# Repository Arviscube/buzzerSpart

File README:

## INSTALLATION
- git clone
- sudo apt install nodejs
- sudo apt install npm
- npm install

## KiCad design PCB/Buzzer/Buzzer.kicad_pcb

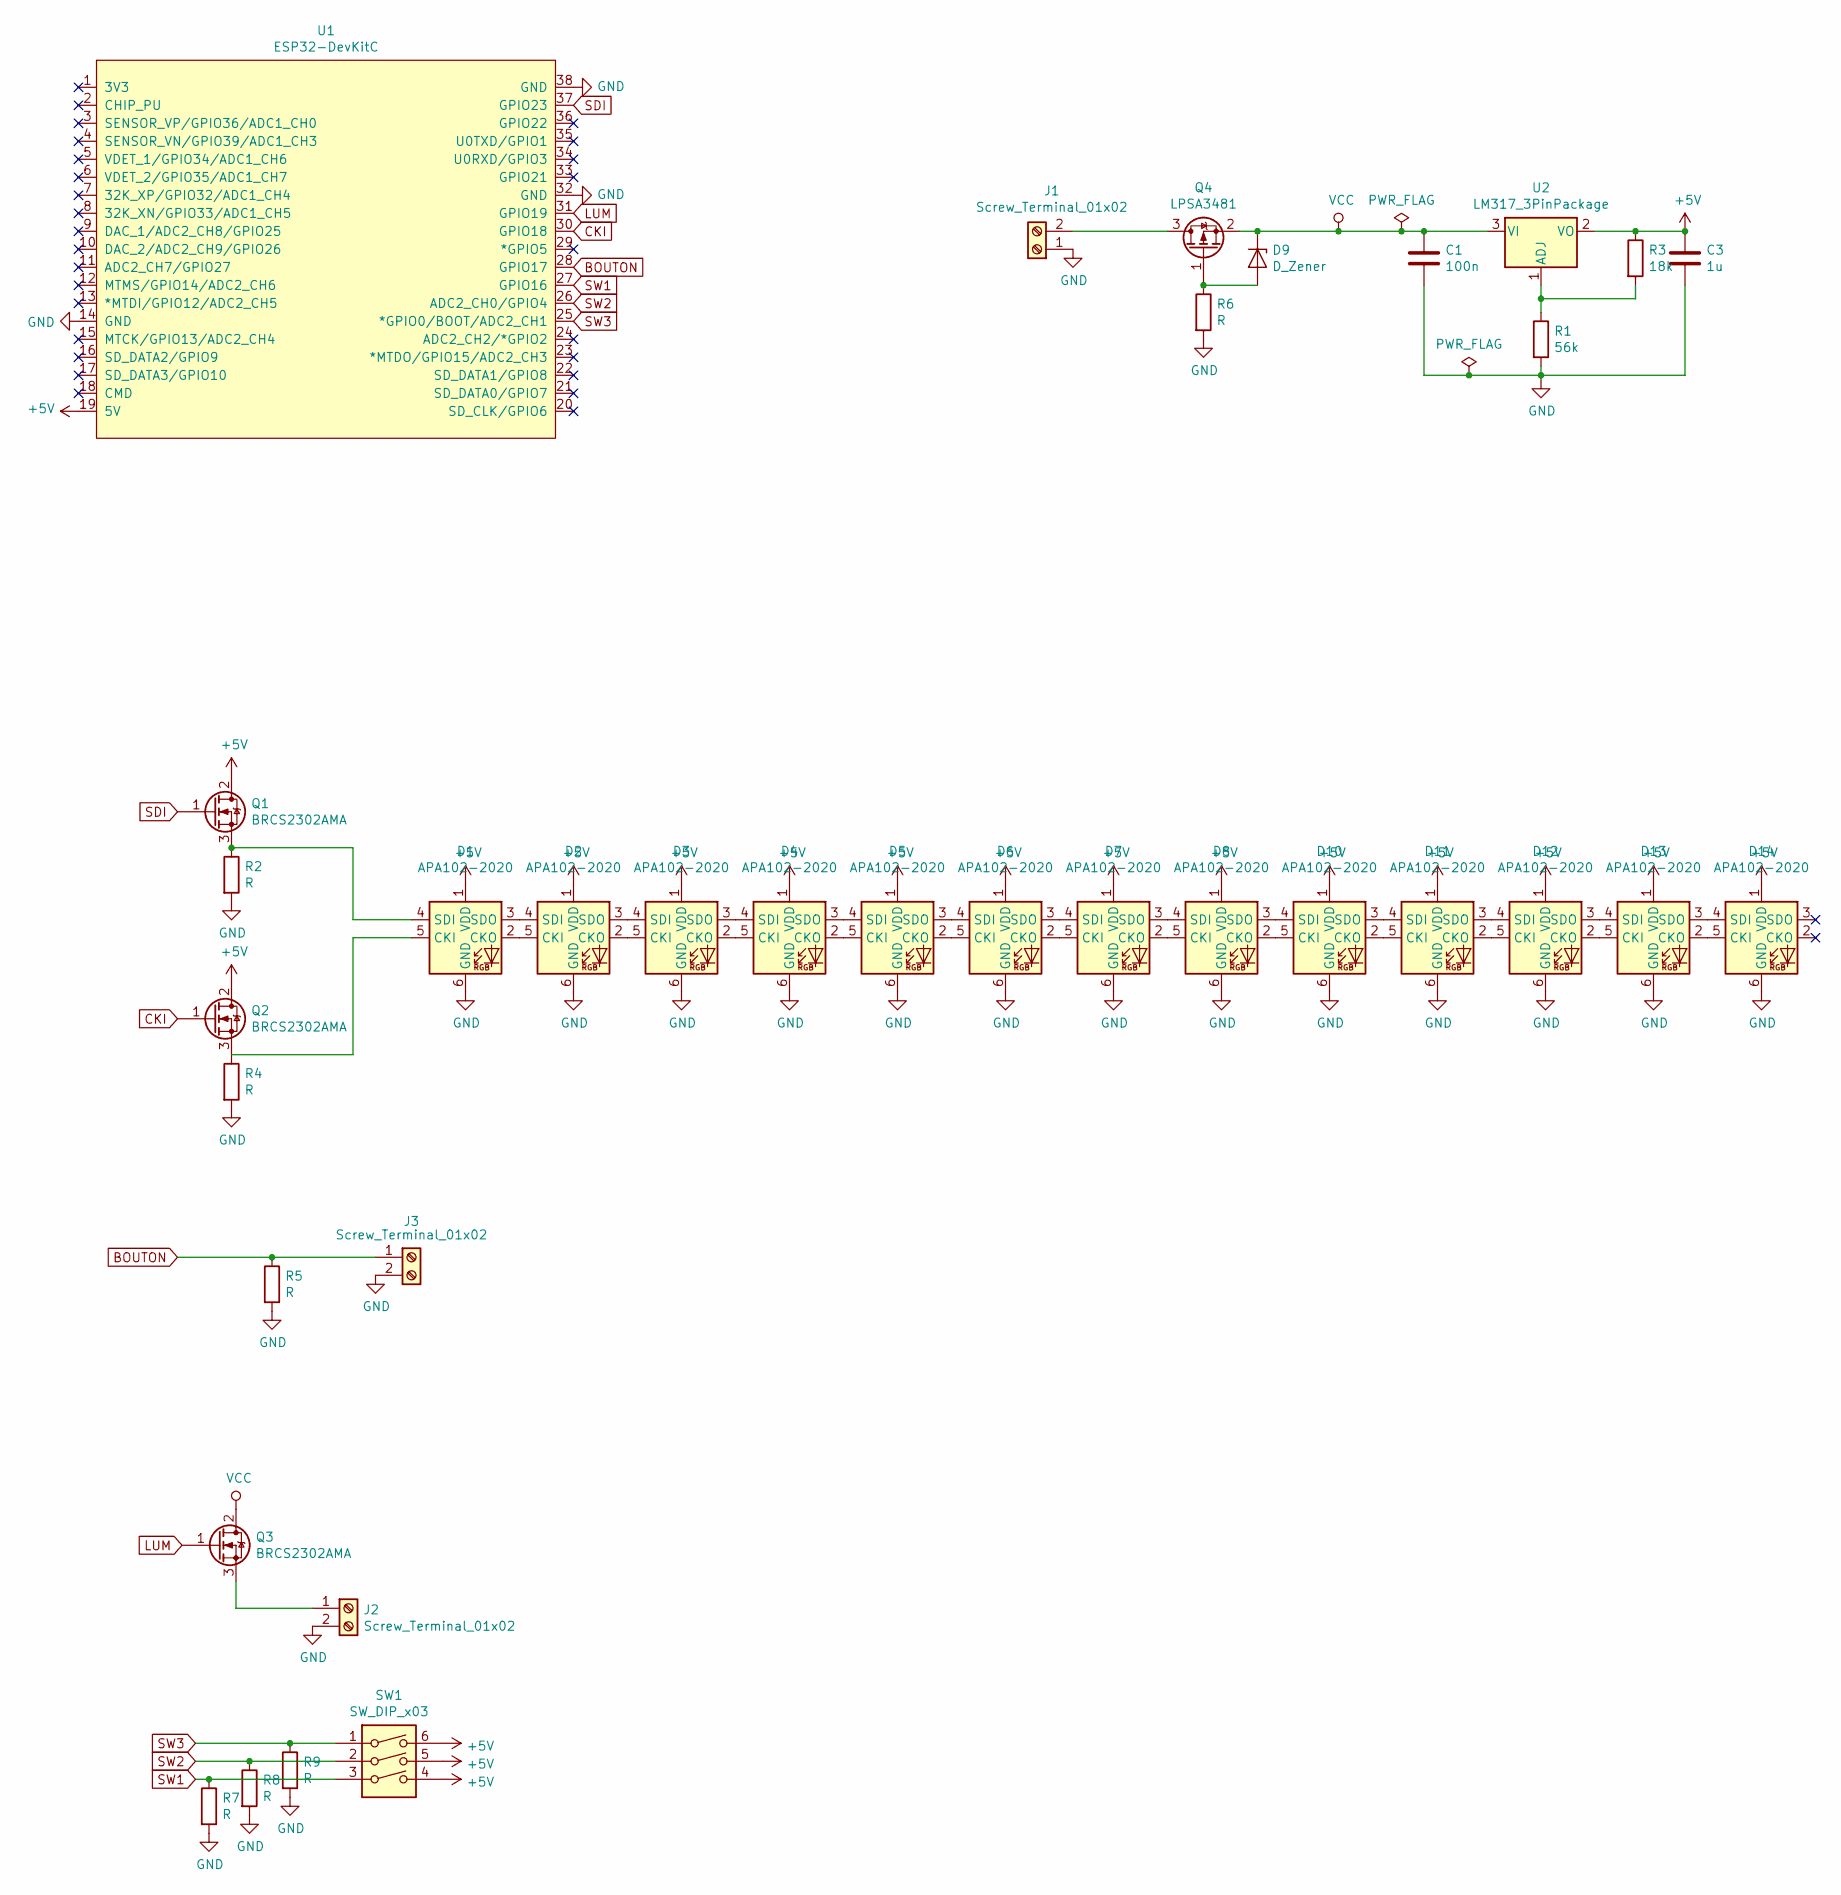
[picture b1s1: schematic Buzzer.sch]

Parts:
C1: 100n; C_0805_2012Metric
C3: 1u; C_0805_2012Metric
D1, D2, D3, D4, D5, D6, D7, D8, D10, D11, D12, D13, D14: APA102-2020; LED-APA102-2020
D9: D_Zener; D_SOD-123
J1, J2, J3: Screw_Terminal_01x02; TerminalBlock_bornier-2_P5.08mm
Q1, Q2, Q3: BRCS2302AMA; SOT-23
Q4: LPSA3481; SOT-23
R1: 56k; R_0805_2012Metric
R2, R4, R5, R6, R7, R8, R9: R; R_0805_2012Metric
R3: 18k; R_0805_2012Metric
SW1: SW_DIP_x03; SW_DIP_SPSTx03_Slide_9.78x9.8mm_W7.62mm_P2.54mm
U1: ESP32-DevKitC
U2: LM317_3PinPackage; TO-252-2

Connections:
+5V: C3.1, D1.1 (VDD), D2.1 (VDD), D3.1 (VDD), D4.1 (VDD), D5.1 (VDD), D6.1 (VDD), D7.1 (VDD), D8.1 (VDD), D10.1 (VDD), D11.1 (VDD), D12.1 (VDD), D13.1 (VDD), D14.1 (VDD), Q1.2 (D), Q2.2 (D), R3.1, SW1.4, SW1.5, SW1.6, U1.19 (5V), U2.2 (VO)
BOUTON: J3.1, R5.1, U1.28 (GPIO17)
CKI: Q2.1 (G), U1.30 (GPIO18)
GND: C1.2, C3.2, D1.6 (GND), D2.6 (GND), D3.6 (GND), D4.6 (GND), D5.6 (GND), D6.6 (GND), D7.6 (GND), D8.6 (GND), D10.6 (GND), D11.6 (GND), D12.6 (GND), D13.6 (GND), D14.6 (GND), J1.1, J2.2, J3.2, R1.2, R2.2, R4.2, R5.2, R6.2, R7.2, R8.2, R9.2, U1.14 (GND), U1.32 (GND), U1.38 (GND)
LUM: Q3.1 (G), U1.31 (GPIO19)
unnamed: D1.2 (CKO), D2.5 (CKI)
unnamed: D1.3 (SDO), D2.4 (SDI)
unnamed: D1.4 (SDI), Q1.3 (S), R2.1
unnamed: D1.5 (CKI), Q2.3 (S), R4.1
unnamed: D2.2 (CKO), D3.5 (CKI)
unnamed: D2.3 (SDO), D3.4 (SDI)
unnamed: D3.2 (CKO), D4.5 (CKI)
unnamed: D3.3 (SDO), D4.4 (SDI)
unnamed: D4.2 (CKO), D5.5 (CKI)
unnamed: D4.3 (SDO), D5.4 (SDI)
unnamed: D5.2 (CKO), D6.5 (CKI)
unnamed: D5.3 (SDO), D6.4 (SDI)
unnamed: D6.2 (CKO), D7.5 (CKI)
unnamed: D6.3 (SDO), D7.4 (SDI)
unnamed: D7.2 (CKO), D8.5 (CKI)
unnamed: D7.3 (SDO), D8.4 (SDI)
unnamed: D9.2 (A), Q4.1 (G), R6.1
unnamed: D10.2 (CKO), D11.5 (CKI)
unnamed: D10.3 (SDO), D11.4 (SDI)
unnamed: D8.3 (SDO), D10.4 (SDI)
unnamed: D8.2 (CKO), D10.5 (CKI)
unnamed: D11.2 (CKO), D12.5 (CKI)
unnamed: D11.3 (SDO), D12.4 (SDI)
unnamed: D12.2 (CKO), D13.5 (CKI)
unnamed: D12.3 (SDO), D13.4 (SDI)
unnamed: D13.2 (CKO), D14.5 (CKI)
unnamed: D13.3 (SDO), D14.4 (SDI)
unnamed: J1.2, Q4.3 (D)
unnamed: J2.1, Q3.3 (S)
unnamed: R1.1, R3.2, U2.1 (ADJ)
SDI: Q1.1 (G), U1.37 (GPIO23)
SW1: R7.1, SW1.3, U1.27 (GPIO16)
SW2: R8.1, SW1.2, U1.26 (ADC2_CH0/GPIO4)
SW3: R9.1, SW1.1, U1.25 (*GPIO0/BOOT/ADC2_CH1)
VCC: C1.1, D9.1 (K), Q3.2 (D), Q4.2 (S), U2.3 (VI)

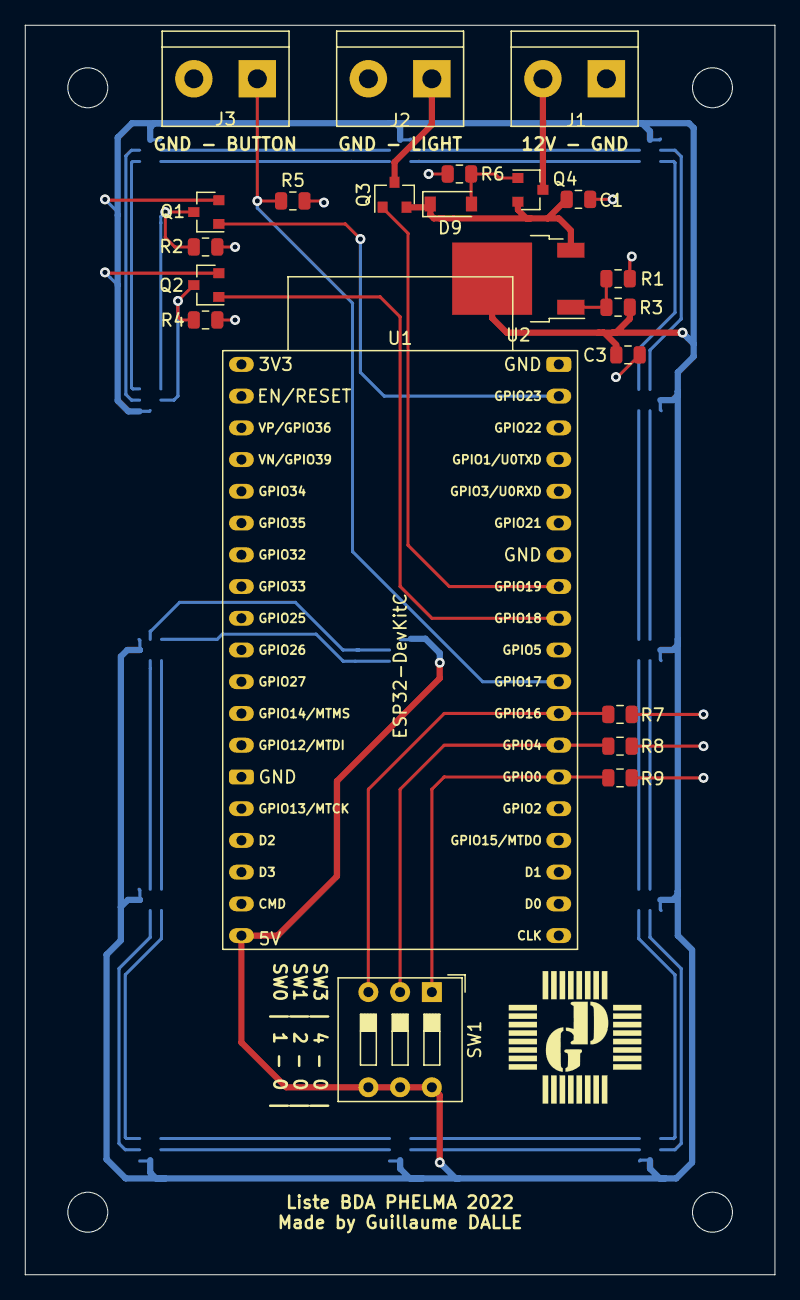
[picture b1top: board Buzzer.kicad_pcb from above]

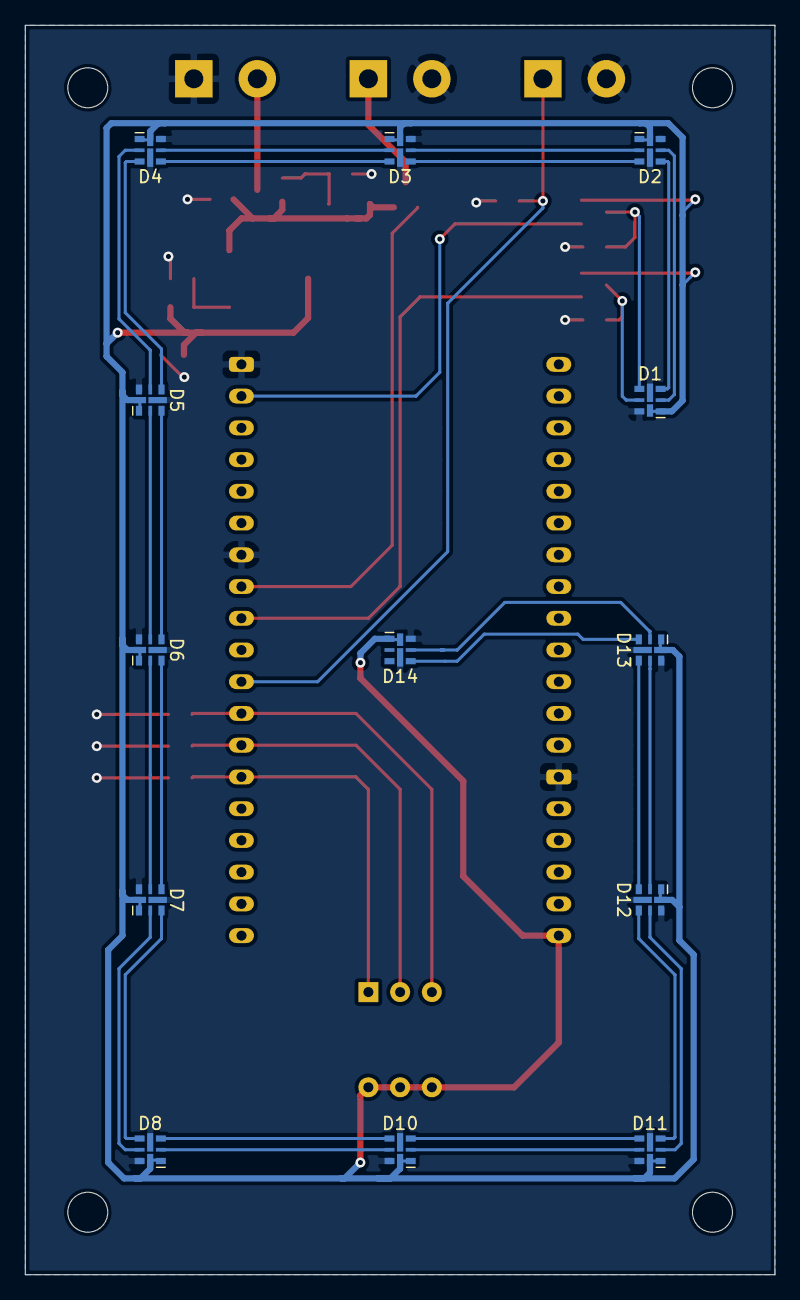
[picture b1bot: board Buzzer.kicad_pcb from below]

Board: 2 copper layers, 60.0 x 100.0 mm, 35 parts (13 on the bottom side), 40 nets.

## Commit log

2023-06-04 remove nodes_modules
2023-06-18 add animation
2023-06-18 add PCB design
2023-06-18 add CAD
2023-08-18 ajout ESP
2023-08-18 auto start
2023-08-18 folder organisation
2023-08-18 small change
2023-08-18 gitignor update
2023-08-18 gitingore
2023-08-18 gitignore modification
2023-08-18 suppression filesé
2023-08-18 corection installation
2023-08-18 add permission
2023-08-21 buzzer client fini
2023-08-23 buzzer whit good address
2023-08-23 bug corection IntallService
2023-08-23 debug info
2023-08-24 EPS32 : adding animations, bug fix, adding auto restart after 10s if the wifi is not available
2023-08-24 interface finished, missing + - button
2023-08-27 add unlock sound
2023-08-29 small change, + - button, bug fix
